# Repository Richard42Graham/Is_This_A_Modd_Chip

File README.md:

# Is_This_A_Modd_Chip

this is the hardware repo for the flatflex mod chip used in the W.I.P bar at Bornhack.

it contains all the kicad files to make the flat flex.

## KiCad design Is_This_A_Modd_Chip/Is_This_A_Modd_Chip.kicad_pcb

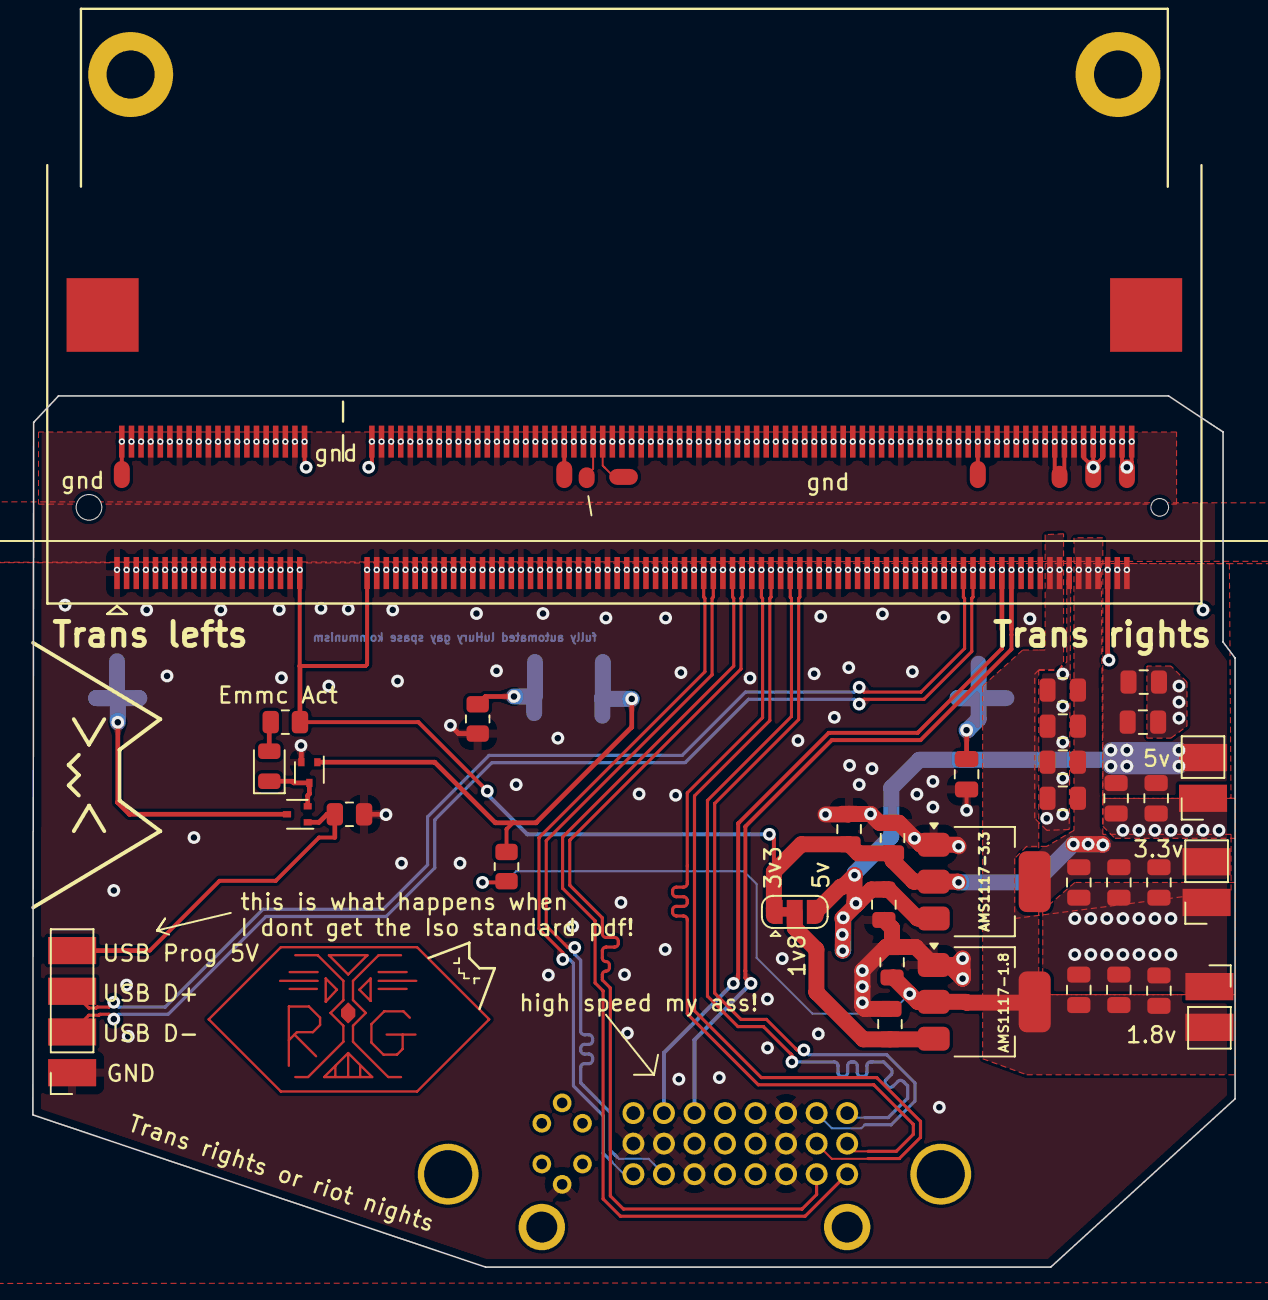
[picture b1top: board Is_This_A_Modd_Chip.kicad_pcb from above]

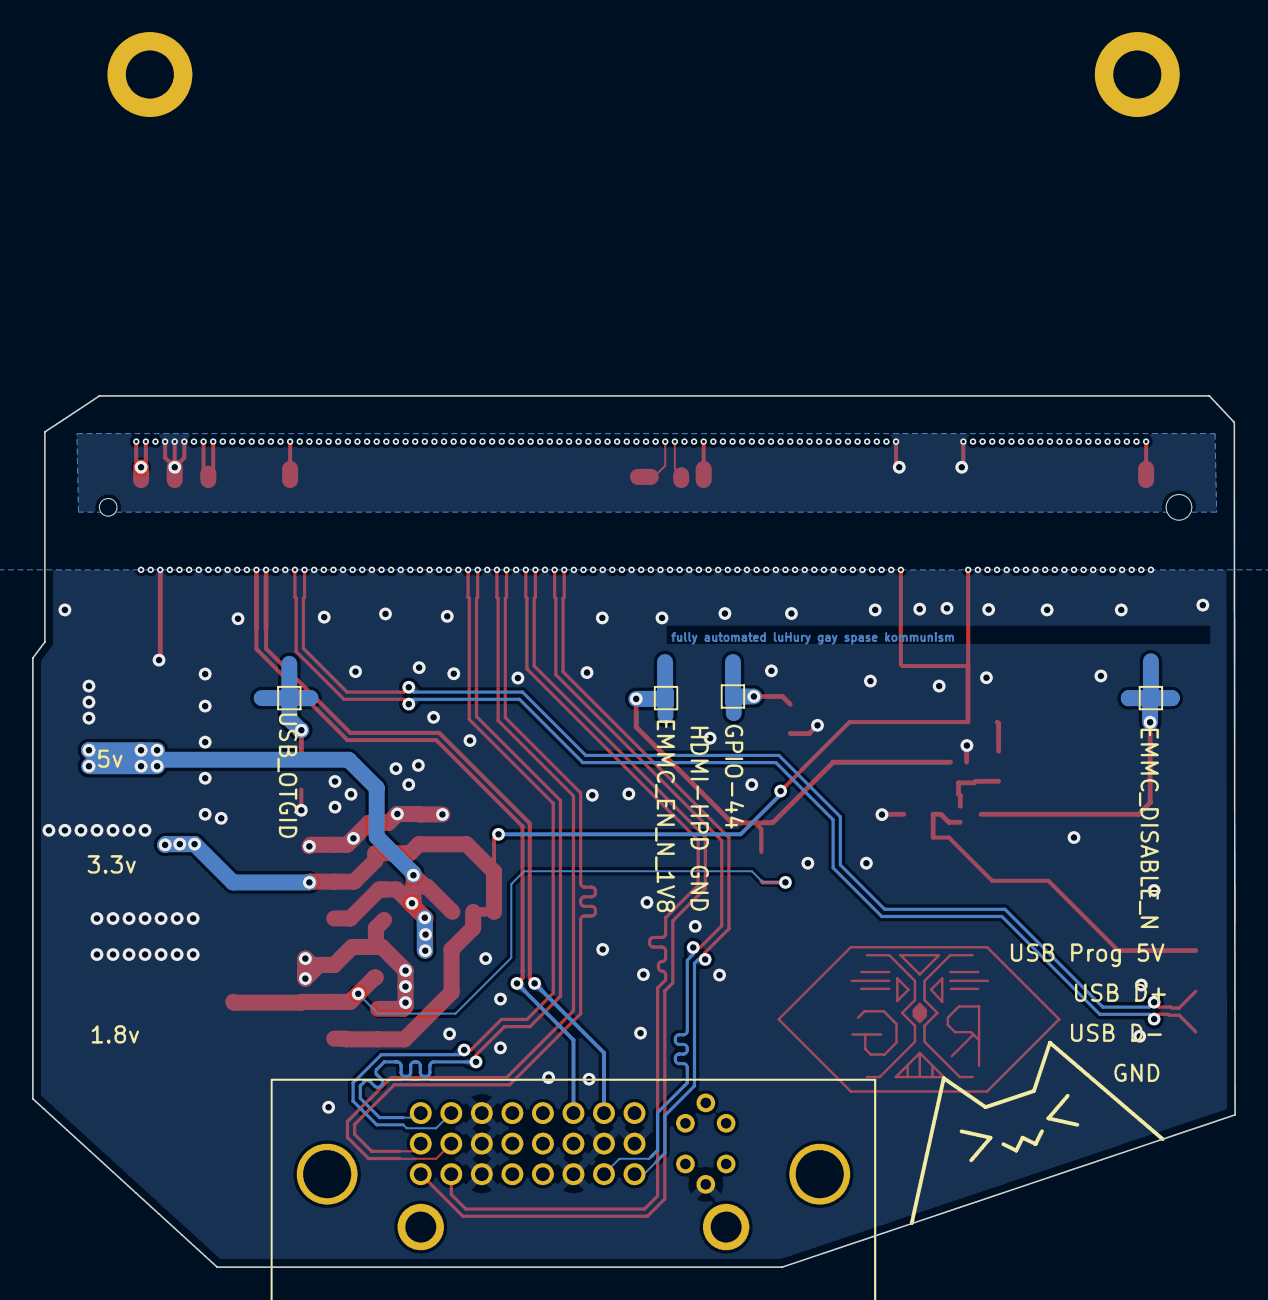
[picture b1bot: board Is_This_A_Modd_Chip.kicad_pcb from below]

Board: 2 copper layers, 75.0 x 54.3 mm, 40 parts (5 on the bottom side), 24 nets.

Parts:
C1, C7, C8, C9, C10, C11, C12, C13, C14, C15, C16, C17, C18, C19: 100nF; C_0805_2012Metric
C2, C3, C4, C5, C6: 10uF; C_0805_2012Metric
D1: LED; LED_0805_2012Metric
J1: SODIMM-200_Split; DDR2_TE_1473149-4
J4: 3.3v; PinSocket_1x02_P2.54mm_Vertical
J7: 5v; PinSocket_1x02_P2.54mm_Vertical
J8: 1.8v; PinSocket_1x02_P2.54mm_Vertical
J9: usb; PinSocket_1x04_P2.54mm_Vertical
JP2: SolderJumper_3_Bridged12; SolderJumper-3_P1.3mm_Bridged12_RoundedPad1.0x1.5mm
K1: 675024321321
Q1, Q2: DMG1012T; SOT-523
R1: 1K; C_0805_2012Metric
R2: 47K; R_0805_2012Metric
R3, R6: 100K; R_0805_2012Metric
R4: 470r; R_0805_2012Metric
TP1: EMMC_EN_N_1V8; TestPoint_Pad_1.0x1.0mm
TP2: EMMC_DISABLE_N; TestPoint_Pad_1.0x1.0mm
TP3: GPIO-44; TestPoint_Pad_1.0x1.0mm
TP4: USB_OTGID; TestPoint_Pad_1.0x1.0mm
U1: AMS1117-3.3; SOT-223-3_TabPin2
U2: AMS1117-1.8; SOT-223-3_TabPin2

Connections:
1V8: C5.1, C7.1, C10.1, C11.1, J1.183, J1.184, J1.185, J1.186, J8.2, R3.1, U2.2 (VO)
3V3: C3.1, C9.1, C12.1, C13.1, C14.1, C15.1, C16.1, C17.1, C18.1, J1.39, J1.40, J1.41, J1.42, J1.189, J1.190, J1.191, J1.192, J1.193, J1.194, J4.2, JP2.1 (A), R4.1, U1.2 (VO)
/CM3 Pins/GPIO44: J1.82, R6.1, TP3.1
/CM3 Pins/HDMI_CLK_N: J1.111, K1.24 (TMDS_Clock_-)
/CM3 Pins/HDMI_CLK_P: J1.113, K1.23 (TMDS_Clock_+)
/CM3 Pins/HDMI_D0_N: J1.117, K1.17 (TMDS_Data_0-)
/CM3 Pins/HDMI_D0_P: J1.119, K1.18 (TMDS_Data_0+)
/CM3 Pins/HDMI_D1_N: J1.123, K1.9 (TMDS_Data_1-)
/CM3 Pins/HDMI_D1_P: J1.125, K1.10 (TMDS_Data_1+)
/CM3 Pins/HDMI_D2_N: J1.129, K1.1 (TMDS_Data_2-)
/CM3 Pins/HDMI_D2_P: J1.131, K1.2 (TMDS_Data_2+)
/CM3 Pins/HDMI_SCL: J1.175, K1.6 (DDC_Clock)
/CM3 Pins/HDMI_SDA: J1.173, K1.7 (DDC_Data)
/CM3 Pins/USB_D_N: J1.167, J9.2
/CM3 Pins/USB_D_P: J1.165, J9.3
/CM3 Pins/USB_OTGID: J1.168, R1.1, TP4.1
EMMC_DISABLE_N: J1.2, Q2.3 (D), TP2.1
EMMC_EN_N_1V8: J1.90, Q1.1 (G), R3.2, TP1.1
GND: C1.2, C2.2, C3.2, C4.2, C5.2, C6.2, C7.2, C8.2, C9.2, C10.2, C11.2, C12.2, C13.2, C14.2, C15.2, C16.2, C17.2, C18.2, C19.2, J1.1, J1.7, J1.8, J1.13, J1.14, J1.19, J1.20, J1.25, J1.26, J1.31, J1.32, J1.37, J1.38, J1.43, J1.44, J1.49, J1.50, J1.55, J1.56, J1.61, J1.62, J1.67, J1.68, J1.73, J1.74, J1.79, J1.80, J1.85, J1.86, J1.91, J1.92, J1.97, J1.98, J1.103, J1.104, J1.109, J1.110, J1.115, J1.116, J1.121, J1.122, J1.127, J1.133, J1.134, J1.139, J1.140, J1.145, J1.146, J1.151, J1.152, J1.157, J1.163, J1.164, J1.169, J1.170, J1.181, J1.182, J1.187, J1.188, J1.195, J1.196, J4.1, J7.1, J8.1, J9.1, K1.3 (TMDS_Data_2/4_Shield), K1.11 (TMDS_DATA_1/3_Sheild), K1.15 (GND), K1.16 (Hot_Plug_Detect), K1.19 (TMDS_Data_0/5_Sheild), K1.22 (TMDS_Data_Clock_Sheild), K1.C5 (Analog_GND), Q1.2 (S), R1.2, R2.2, R6.2, U1.1 (GND), U2.1 (GND)
unnamed: D1.2 (A), R4.2
unnamed: D1.1 (K), Q1.3 (D), Q2.2 (S)
unnamed: J9.4, Q2.1 (G), R2.1
unnamed: C4.1, JP2.2 (C), U2.3 (VI)
VBAT: C1.1, C2.1, C6.1, C8.1, C19.1, J1.197, J1.198, J1.199, J1.200, J7.2, JP2.3 (B), U1.3 (VI)

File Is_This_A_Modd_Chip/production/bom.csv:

Designator,Footprint,Quantity,Value,LCSC Part #
"C1, C10, C11, C12, C13, C14, C15, C16, C17, C18, C19, C7, C8, C9",0805,14,100nF,
"C2, C3, C4, C5, C6",0805,5,10uF,
D1,0805,1,LED,
"Q1, Q2",SOT-523,2,DMG1012T,C2830301
R1,0805,1,1K,
R2,0805,1,47K,
"R3, R6",0805,2,100K,
R4,0805,1,470r,
TP2,TestPoint_Pad_1.0x1.0mm,1,EMMC_DISABLE_N,
U2,SOT-223-3_TabPin2,1,AMS1117-1.8,

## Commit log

2024-08-05 added kicad files, and stared the read me.
